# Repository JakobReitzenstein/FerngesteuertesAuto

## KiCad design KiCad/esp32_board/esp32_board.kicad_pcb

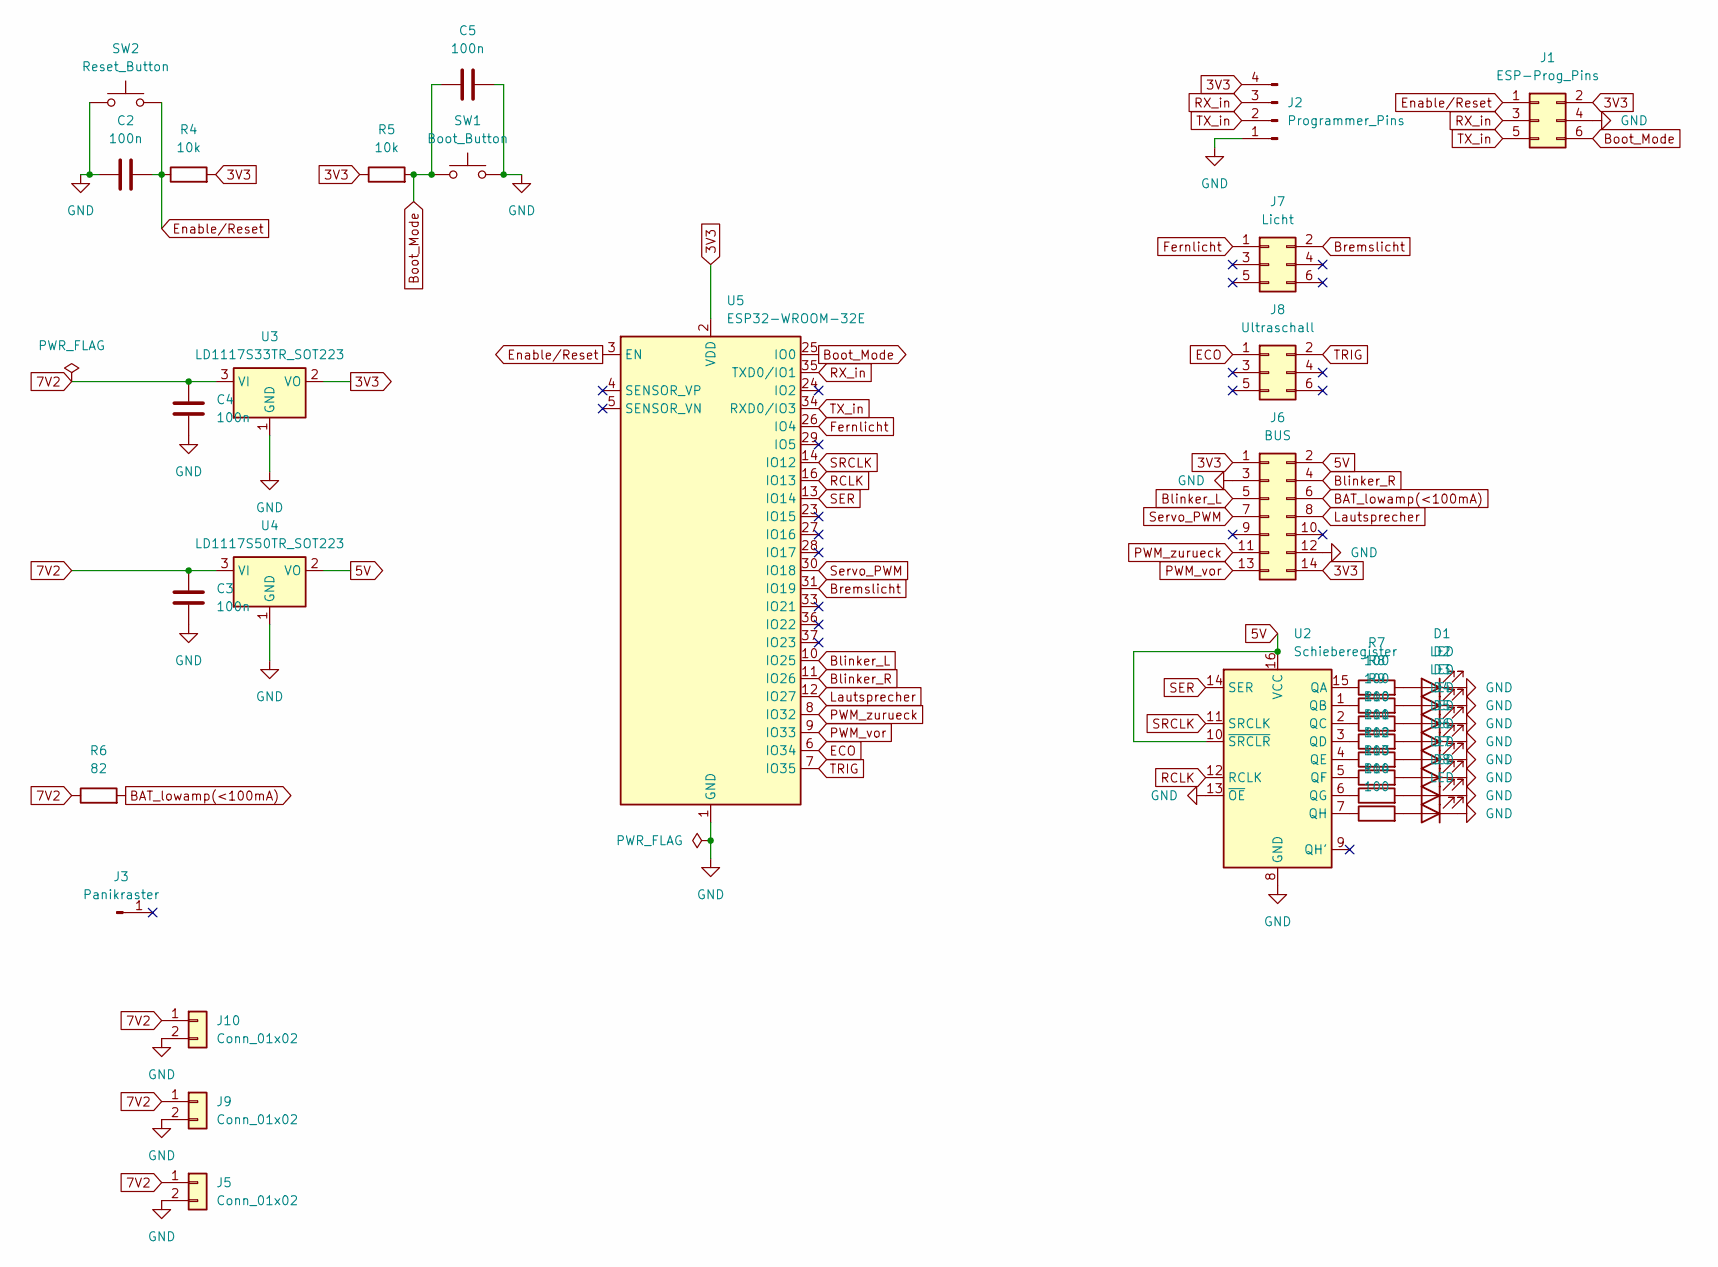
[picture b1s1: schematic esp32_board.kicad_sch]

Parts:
C2, C3, C4, C5: 100n; C_Disc_D3.0mm_W1.6mm_P2.50mm
D1, D2, D3, D4, D5, D6, D7, D8: LED; TestPoint_2Pads_Pitch5.08mm_Drill1.3mm
J1: ESP-Prog_Pins; PinHeader_2x03_P1.27mm_Vertical_SMD
J2: Programmer_Pins; PinHeader_1x04_P2.54mm_Vertical
J3: Panikraster; Panikraster_05x05
J5, J9, J10: Conn_01x02; AMASS_XT30PW-F_1x02_P2.50mm_Horizontal
J6: BUS; Busstecker
J7: Licht; IDC-Header_2x03_P2.54mm_Vertical
J8: Ultraschall; IDC-Header_2x03_P2.54mm_Vertical
R4, R5: 10k; R_Axial_DIN0207_L6.3mm_D2.5mm_P7.62mm_Horizontal
R6: 82; R_Axial_DIN0207_L6.3mm_D2.5mm_P7.62mm_Horizontal
R7, R8, R9, R10, R11, R12, R13, R14: 100; R_Axial_DIN0207_L6.3mm_D2.5mm_P7.62mm_Horizontal
SW1: Boot_Button; SW_PUSH_6mm_H4.3mm
SW2: Reset_Button; SW_PUSH_6mm_H4.3mm
U2: Schieberegister; DIP-16_W7.62mm_LongPads
U3: LD1117S33TR_SOT223; TO-220-3_Vertical
U4: LD1117S50TR_SOT223; TO-220-3_Vertical
U5: ESP32-WROOM-32E; ESP32-WROOM-32_Prolab-Anpassung

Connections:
3V3: J1.2, J2.4, J6.1, J6.14, R4.2, R5.1, U3.2 (VO), U5.2 (VDD)
5V: J6.2, U2.10 (~SRCLR), U2.16 (VCC), U4.2 (VO)
7V2: C3.2, C4.2, J5.1, J9.1, J10.1, R6.1, U3.3 (VI), U4.3 (VI)
BAT_lowamp(<100mA): J6.6, R6.2
Blinker_L: J6.5, U5.10 (IO25)
Blinker_R: J6.4, U5.11 (IO26)
Boot_Mode: C5.1, J1.6, R5.2, SW1.1, U5.25 (IO0)
Bremslicht: J7.2, U5.31 (IO19)
ECO: J8.1, U5.6 (IO34)
Enable/Reset: C2.2, J1.1, R4.1, SW2.2, U5.3 (EN)
Fernlicht: J7.1, U5.26 (IO4)
GND: C2.1, C3.1, C4.1, C5.2, D1.1 (K), D2.1 (K), D3.1 (K), D4.1 (K), D5.1 (K), D6.1 (K), D7.1 (K), D8.1 (K), J1.4, J2.1, J5.2, J6.3, J6.12, J9.2, J10.2, SW1.2, SW2.1, U2.8 (GND), U2.13 (~OE), U3.1 (GND), U4.1 (GND), U5.1 (GND), U5.15 (GND), U5.38 (GND), U5.39 (GND)
Lautsprecher: J6.8, U5.12 (IO27)
unnamed: D1.2 (A), R7.2
unnamed: D2.2 (A), R8.2
unnamed: D3.2 (A), R9.2
unnamed: D4.2 (A), R10.2
unnamed: D5.2 (A), R11.2
unnamed: D6.2 (A), R12.2
unnamed: D7.2 (A), R13.2
unnamed: D8.2 (A), R14.2
unnamed: R7.1, U2.15 (QA)
unnamed: R8.1, U2.1 (QB)
unnamed: R9.1, U2.2 (QC)
unnamed: R10.1, U2.3 (QD)
unnamed: R11.1, U2.4 (QE)
unnamed: R12.1, U2.5 (QF)
unnamed: R13.1, U2.6 (QG)
unnamed: R14.1, U2.7 (QH)
PWM_vor: J6.13, U5.9 (IO33)
PWM_zurueck: J6.11, U5.8 (IO32)
RCLK: U2.12 (RCLK), U5.16 (IO13)
RX_in: J1.3, J2.3, U5.35 (TXD0/IO1)
SER: U2.14 (SER), U5.13 (IO14)
SRCLK: U2.11 (SRCLK), U5.14 (IO12)
Servo_PWM: J6.7, U5.30 (IO18)
TRIG: J8.2, U5.7 (IO35)
TX_in: J1.5, J2.2, U5.34 (RXD0/IO3)

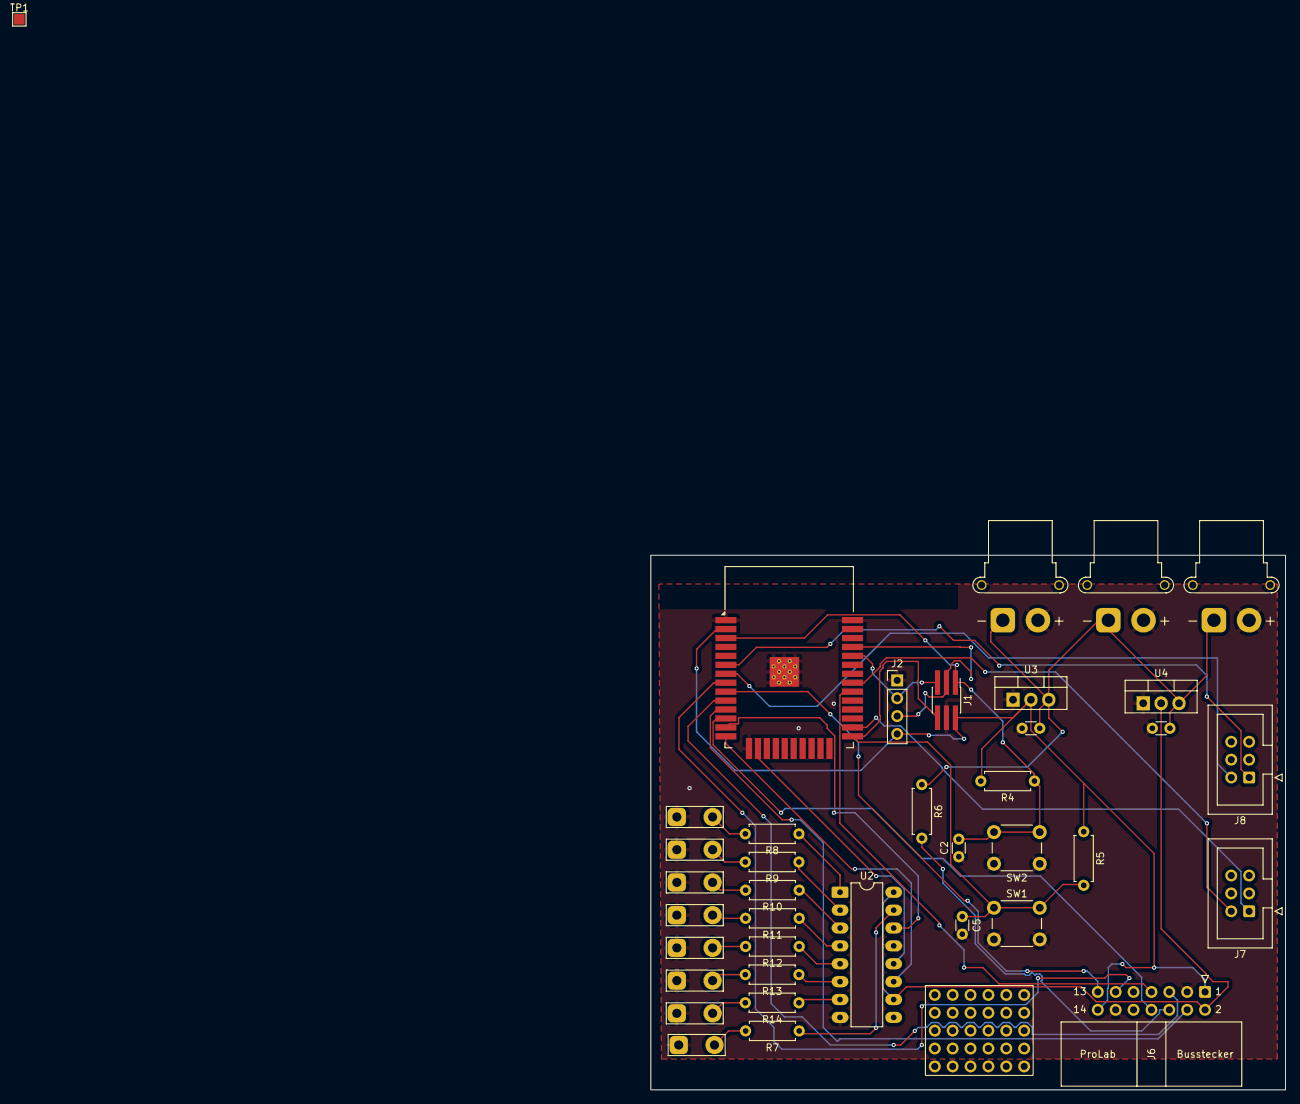
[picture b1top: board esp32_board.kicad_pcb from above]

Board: 2 copper layers, 90.2 x 76.0 mm, 39 parts (0 on the bottom side), 38 nets.

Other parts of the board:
TP1: TestPoint; TestPoint_Pad_1.5x1.5mm

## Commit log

2025-05-20 Initializing the project
2025-05-20 Präsi Hinzugefügt, main datei weiter programmiert
2025-05-27 27.05.2025
2025-05-27 fixed Callback, added fernbedienung code, main.cpp erweitert
2025-06-03 03.06 Stromcheck eingefügt, Motorpins Vorwärts/ Rückwärts
2025-06-10 Added StatusLEDs, Fernbedienung Code
2025-07-01 01.07
2025-07-11 11.07
2025-07-15 15.07
